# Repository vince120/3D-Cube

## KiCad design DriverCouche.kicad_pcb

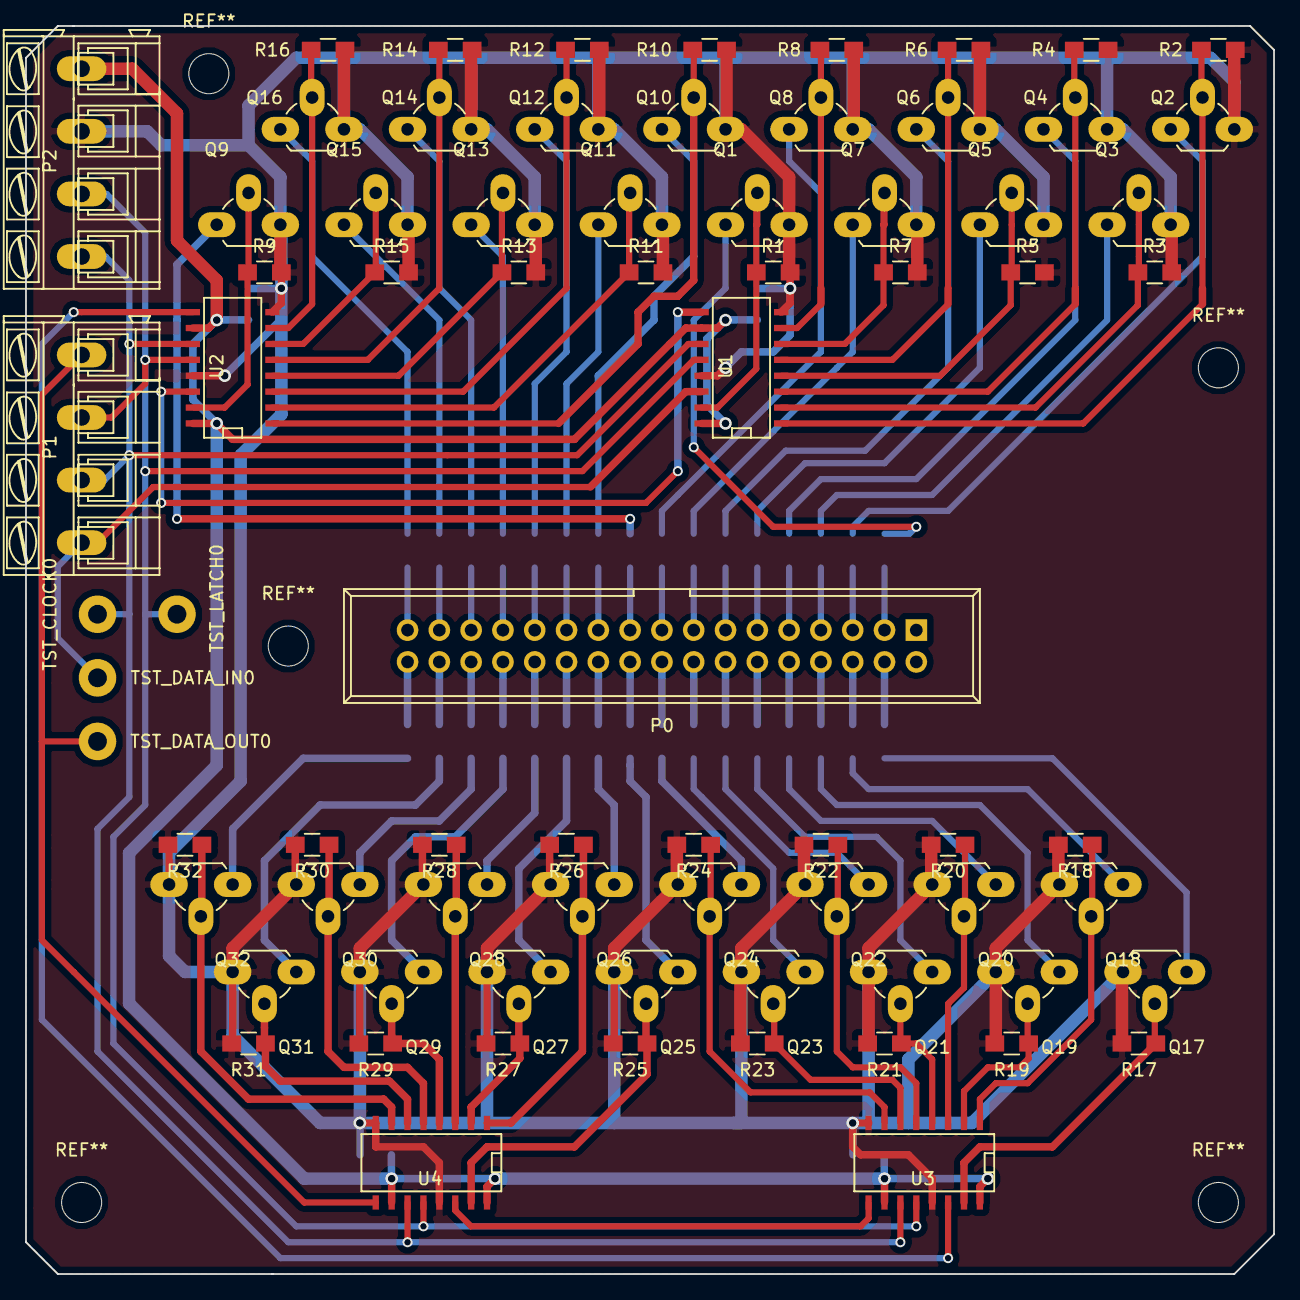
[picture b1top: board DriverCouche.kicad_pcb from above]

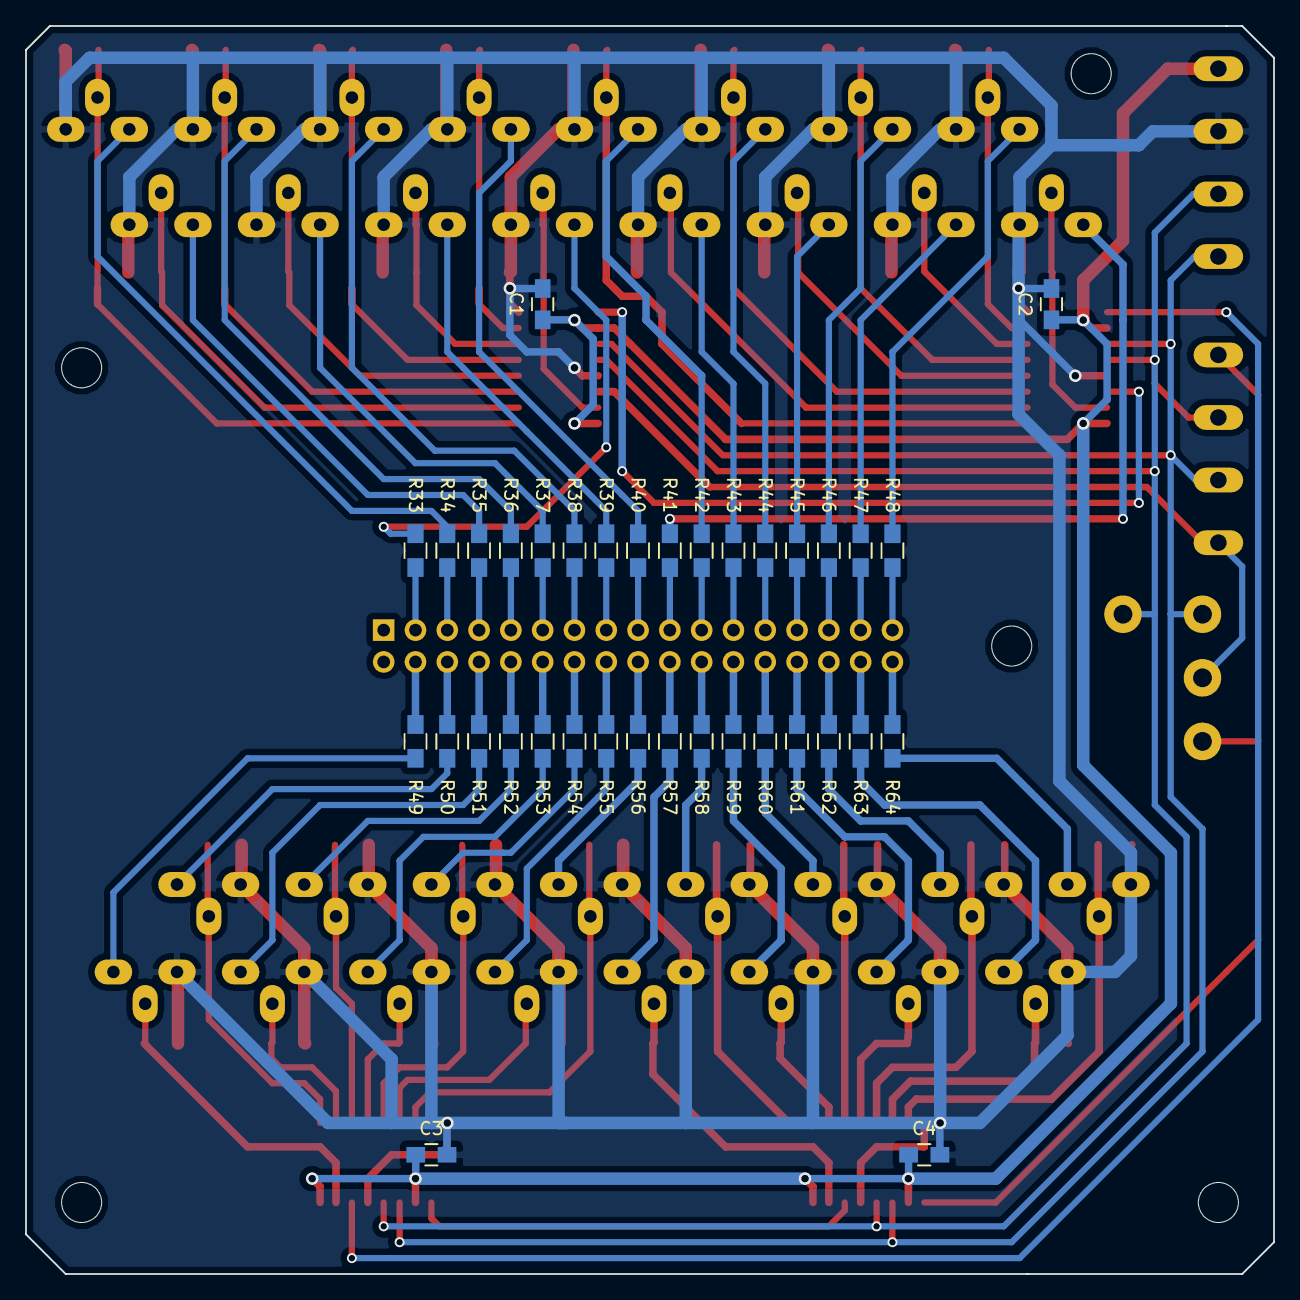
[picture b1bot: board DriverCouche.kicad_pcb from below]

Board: 2 copper layers, 99.7 x 99.7 mm, 111 parts (36 on the bottom side), 105 nets.

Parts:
C1, C2, C3, C4: C; C_0805_HandSoldering
P0: HE10-34; IDC_Header_Straight_34pins
P1, P2: CONN_01X04; AK300-4
Q1, Q2, Q3, Q4, Q5, Q6, Q7, Q8, Q9, Q10, Q11, Q12, Q13, Q14, Q15, Q16, Q17, Q18, Q19, Q20, Q21, Q22, Q23, Q24, Q25, Q26, Q27, Q28, Q29, Q30, Q31, Q32: BS170; TO-92_Rugged
R1, R2, R3, R4, R5, R6, R7, R8, R9, R10, R11, R12, R13, R14, R15, R16, R17, R18, R19, R20, R21, R22, R23, R24, R25, R26, R27, R28, R29, R30, R31, R32, R33, R34, R35, R36, R37, R38, R39, R40, R41, R42, R43, R44, R45, R46, R47, R48, R49, R50, R51, R52, R53, R54, R55, R56, R57, R58, R59, R60, R61, R62, R63, R64: R; R_0805_HandSoldering
TST_CLOCK0: TEST_1P; Measurement_Point_Round-TH_Big
TST_DATA_IN0: TEST_1P; Measurement_Point_Round-TH_Big
TST_DATA_OUT0: TEST_1P; Measurement_Point_Round-TH_Big
TST_LATCH0: TEST_1P; Measurement_Point_Round-TH_Big
U1, U2, U3, U4: 74HC595; SO-16-N

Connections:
/CLOCK: P1.2, P2.1, TST_CLOCK0.1, U1.11, U2.11, U3.11, U4.11
/DATA_IN: P1.1, TST_DATA_IN0.1, U1.14
/DATA_OUT: P1.4, TST_DATA_OUT0.1, U4.9
/LATCH: P1.3, P2.2, TST_LATCH0.1, U1.12, U2.12, U3.12, U4.12
GND: C1.2, C2.2, C3.2, C4.2, P2.3, Q1.3, Q2.3, Q3.3, Q4.3, Q5.3, Q6.3, Q7.3, Q8.3, Q9.3, Q10.3, Q11.3, Q12.3, Q13.3, Q14.3, Q15.3, Q16.3, Q17.3, Q18.3, Q19.3, Q20.3, Q21.3, Q22.3, Q23.3, Q24.3, Q25.3, Q26.3, Q27.3, Q28.3, Q29.3, Q30.3, Q31.3, Q32.3, R1.2, R2.2, R3.2, R4.2, R5.2, R6.2, R7.2, R8.2, R9.2, R10.2, R11.2, R12.2, R13.2, R14.2, R15.2, R16.2, R17.2, R18.2, R19.2, R20.2, R21.2, R22.2, R23.2, R24.2, R25.2, R26.2, R27.2, R28.2, R29.2, R30.2, R31.2, R32.2, U1.8, U1.13, U2.8, U2.13, U3.8, U3.13, U4.8, U4.13
unnamed: P0.3, R33.2
unnamed: P0.4, R49.1
unnamed: P0.5, R34.1
unnamed: P0.6, R50.2
unnamed: P0.7, R35.1
unnamed: P0.8, R51.2
unnamed: P0.9, R36.1
unnamed: P0.10, R52.2
unnamed: P0.11, R37.2
unnamed: P0.12, R53.1
unnamed: P0.13, R38.1
unnamed: P0.14, R54.2
unnamed: P0.15, R39.1
unnamed: P0.16, R55.2
unnamed: P0.17, R40.1
unnamed: P0.18, R56.2
unnamed: P0.19, R41.2
unnamed: P0.20, R57.1
unnamed: P0.21, R42.1
unnamed: P0.22, R58.2
unnamed: P0.23, R43.1
unnamed: P0.24, R59.2
unnamed: P0.25, R44.1
unnamed: P0.26, R60.2
unnamed: P0.27, R45.2
unnamed: P0.28, R61.1
unnamed: P0.29, R46.1
unnamed: P0.30, R62.2
unnamed: P0.31, R47.1
unnamed: P0.32, R63.2
unnamed: P0.33, R48.1
unnamed: P0.34, R64.2
unnamed: Q1.1, R33.1
unnamed: Q1.2, R1.1, U1.15
unnamed: Q2.1, R34.2
unnamed: Q2.2, R2.1, U1.1
unnamed: Q3.1, R35.2
unnamed: Q3.2, R3.1, U1.2
unnamed: Q4.1, R36.2
unnamed: Q4.2, R4.1, U1.3
unnamed: Q5.1, R37.1
unnamed: Q5.2, R5.1, U1.4
unnamed: Q6.1, R38.2
unnamed: Q6.2, R6.1, U1.5
unnamed: Q7.1, R39.2
unnamed: Q7.2, R7.1, U1.6
unnamed: Q8.1, R40.2
unnamed: Q8.2, R8.1, U1.7
unnamed: Q9.1, R41.1
unnamed: Q9.2, R9.1, U2.15
unnamed: Q10.1, R42.2
unnamed: Q10.2, R10.1, U2.1
unnamed: Q11.1, R43.2
unnamed: Q11.2, R11.1, U2.2
unnamed: Q12.1, R44.2
unnamed: Q12.2, R12.1, U2.3
unnamed: Q13.1, R45.1
unnamed: Q13.2, R13.1, U2.4
unnamed: Q14.1, R46.2
unnamed: Q14.2, R14.1, U2.5
unnamed: Q15.1, R47.2
unnamed: Q15.2, R15.1, U2.6
unnamed: Q16.1, R48.2
unnamed: Q16.2, R16.1, U2.7
unnamed: Q17.1, R49.2
unnamed: Q17.2, R17.1, U3.15
unnamed: Q18.1, R50.1
unnamed: Q18.2, R18.1, U3.1
unnamed: Q19.1, R51.1
unnamed: Q19.2, R19.1, U3.2
unnamed: Q20.1, R52.1
unnamed: Q20.2, R20.1, U3.3
unnamed: Q21.1, R53.2
unnamed: Q21.2, R21.1, U3.4
unnamed: Q22.1, R54.1
unnamed: Q22.2, R22.1, U3.5
unnamed: Q23.1, R55.1
unnamed: Q23.2, R23.1, U3.6
unnamed: Q24.1, R56.1
unnamed: Q24.2, R24.1, U3.7
unnamed: Q25.1, R57.2
unnamed: Q25.2, R25.1, U4.15
unnamed: Q26.1, R58.1
unnamed: Q26.2, R26.1, U4.1
unnamed: Q27.1, R59.1
unnamed: Q27.2, R27.1, U4.2
unnamed: Q28.1, R60.1
unnamed: Q28.2, R28.1, U4.3
unnamed: Q29.1, R61.2
unnamed: Q29.2, R29.1, U4.4
unnamed: Q30.1, R62.1
unnamed: Q30.2, R30.1, U4.5
unnamed: Q31.1, R63.1
unnamed: Q31.2, R31.1, U4.6
unnamed: Q32.1, R64.1
unnamed: Q32.2, R32.1, U4.7
unnamed: U1.9, U2.14
unnamed: U2.9, U3.14
unnamed: U3.9, U4.14
VCC: C1.1, C2.1, C3.1, C4.1, P2.4, U1.10, U1.16, U2.10, U2.16, U3.10, U3.16, U4.10, U4.16

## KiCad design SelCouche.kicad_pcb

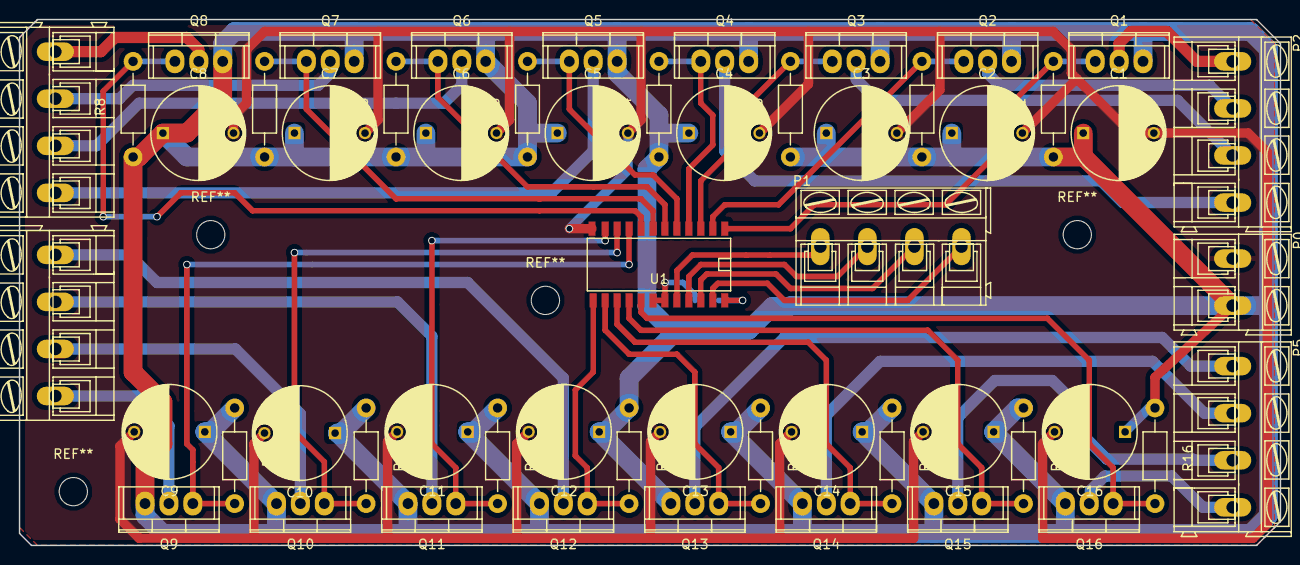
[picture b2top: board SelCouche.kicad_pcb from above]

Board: 2 copper layers, 134.0 x 55.9 mm, 56 parts (1 on the bottom side), 38 nets.

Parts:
C1, C2, C3, C4, C5, C6, C7, C8, C9, C10, C11, C12, C13, C14, C15, C16: C; C_Radial_D10_L20_P7.5
C17: C; C_0805_HandSoldering
P0: CONN_01X02; AK300-2
P1, P2, P3, P4, P5: CONN_01X04; AK300-4
Q1, Q2, Q3, Q4, Q5, Q6, Q7, Q8, Q9, Q10, Q11, Q12, Q13, Q14, Q15, Q16: IRF9540N; TO-220
R1, R2, R3, R4, R5, R6, R7, R8, R9, R10, R11, R12, R13, R14, R15, R16: R; Resistor_Horizontal_RM10mm
U1: 74LS154; SOIC-24

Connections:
/Couche01: P2.1, Q1.2
/Couche02: P2.2, Q2.2
/Couche03: P2.3, Q3.2
/Couche04: P2.4, Q4.2
/Couche05: P3.1, Q5.2
/Couche06: P3.2, Q6.2
/Couche07: P3.3, Q7.2
/Couche08: P3.4, Q8.2
/Couche09: P4.1, Q9.2
/Couche10: P4.2, Q10.2
/Couche11: P4.3, Q11.2
/Couche12: P4.4, Q12.2
/Couche13: P5.1, Q13.2
/Couche14: P5.2, Q14.2
/Couche15: P5.3, Q15.2
/Couche16: P5.4, Q16.2
GND: C1.2, C2.2, C3.2, C4.2, C5.2, C6.2, C7.2, C8.2, C9.2, C10.2, C11.2, C12.2, C13.2, C14.2, C15.2, C16.2, C17.2, P0.1, U1.12, U1.18, U1.19
unnamed: P1.1, U1.20
unnamed: P1.2, U1.21
unnamed: P1.3, U1.22
unnamed: P1.4, U1.23
unnamed: Q1.1, R1.2, U1.1
unnamed: Q2.1, R2.2, U1.2
unnamed: Q3.1, R3.2, U1.3
unnamed: Q4.1, R4.2, U1.4
unnamed: Q5.1, R5.2, U1.5
unnamed: Q6.1, R6.2, U1.6
unnamed: Q7.1, R7.2, U1.7
unnamed: Q8.1, R8.2, U1.8
unnamed: Q9.1, R9.2, U1.9
unnamed: Q10.1, R10.2, U1.10
unnamed: Q11.1, R11.2, U1.11
unnamed: Q12.1, R12.2, U1.13
unnamed: Q13.1, R13.2, U1.14
unnamed: Q14.1, R14.2, U1.15
unnamed: Q15.1, R15.2, U1.16
unnamed: Q16.1, R16.2, U1.17
VCC: C1.1, C2.1, C3.1, C4.1, C5.1, C6.1, C7.1, C8.1, C9.1, C10.1, C11.1, C12.1, C13.1, C14.1, C15.1, C16.1, C17.1, P0.2, Q1.3, Q2.3, Q3.3, Q4.3, Q5.3, Q6.3, Q7.3, Q8.3, Q9.3, Q10.3, Q11.3, Q12.3, Q13.3, Q14.3, Q15.3, Q16.3, R1.1, R2.1, R3.1, R4.1, R5.1, R6.1, R7.1, R8.1, R9.1, R10.1, R11.1, R12.1, R13.1, R14.1, R15.1, R16.1, U1.24

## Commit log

2019-12-16 Base, Selcouche and Driver
